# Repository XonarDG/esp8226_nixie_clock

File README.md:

# esp8266_nixie_clock

Simple Nixie Clock with an ESP8266 development board

## Info

This is a small project for a simple nixie clock using a ESP8266 development board. **WIP! USE AS REFERENCE ONLY!**

## Why?
Like many others, I've fallen for the look of nixies way before this project began. At the time I thought I wasn't capable of a project like this, but in late 2021 I made my first prototype using MH74141 and Tesla ZM1020 nixies. It was rough, didn't work properly and was on a protoboard, but it motivated me into doing more.

In 2024 I made the decision to make this my high school graduation project and this is what came out of it. It still has rough edges here and there, but it works, and it has a somewhat complete enclosure.

At this point I thought it would be a nice touch making the project publicly available. That said its far from done, and I would not recommend making this project on your own.

## Parts
Name | Designation | #
--- | --- | ---
MCU | Wemos D1 Mini | 1
RTC module | generic DS3231 | 1
Shift Register | 74HC595 | 3
Cathode transistors | MPSA42 | 10
Anode optoucouplers | TLP627 | 6
Voltage Regulator | AMS1117 3.3 | 1
Resistor | various values | 26
Pin header (male) | generic 2.54mm | 21
Pin header (famale) | generic 2.54mm | 46

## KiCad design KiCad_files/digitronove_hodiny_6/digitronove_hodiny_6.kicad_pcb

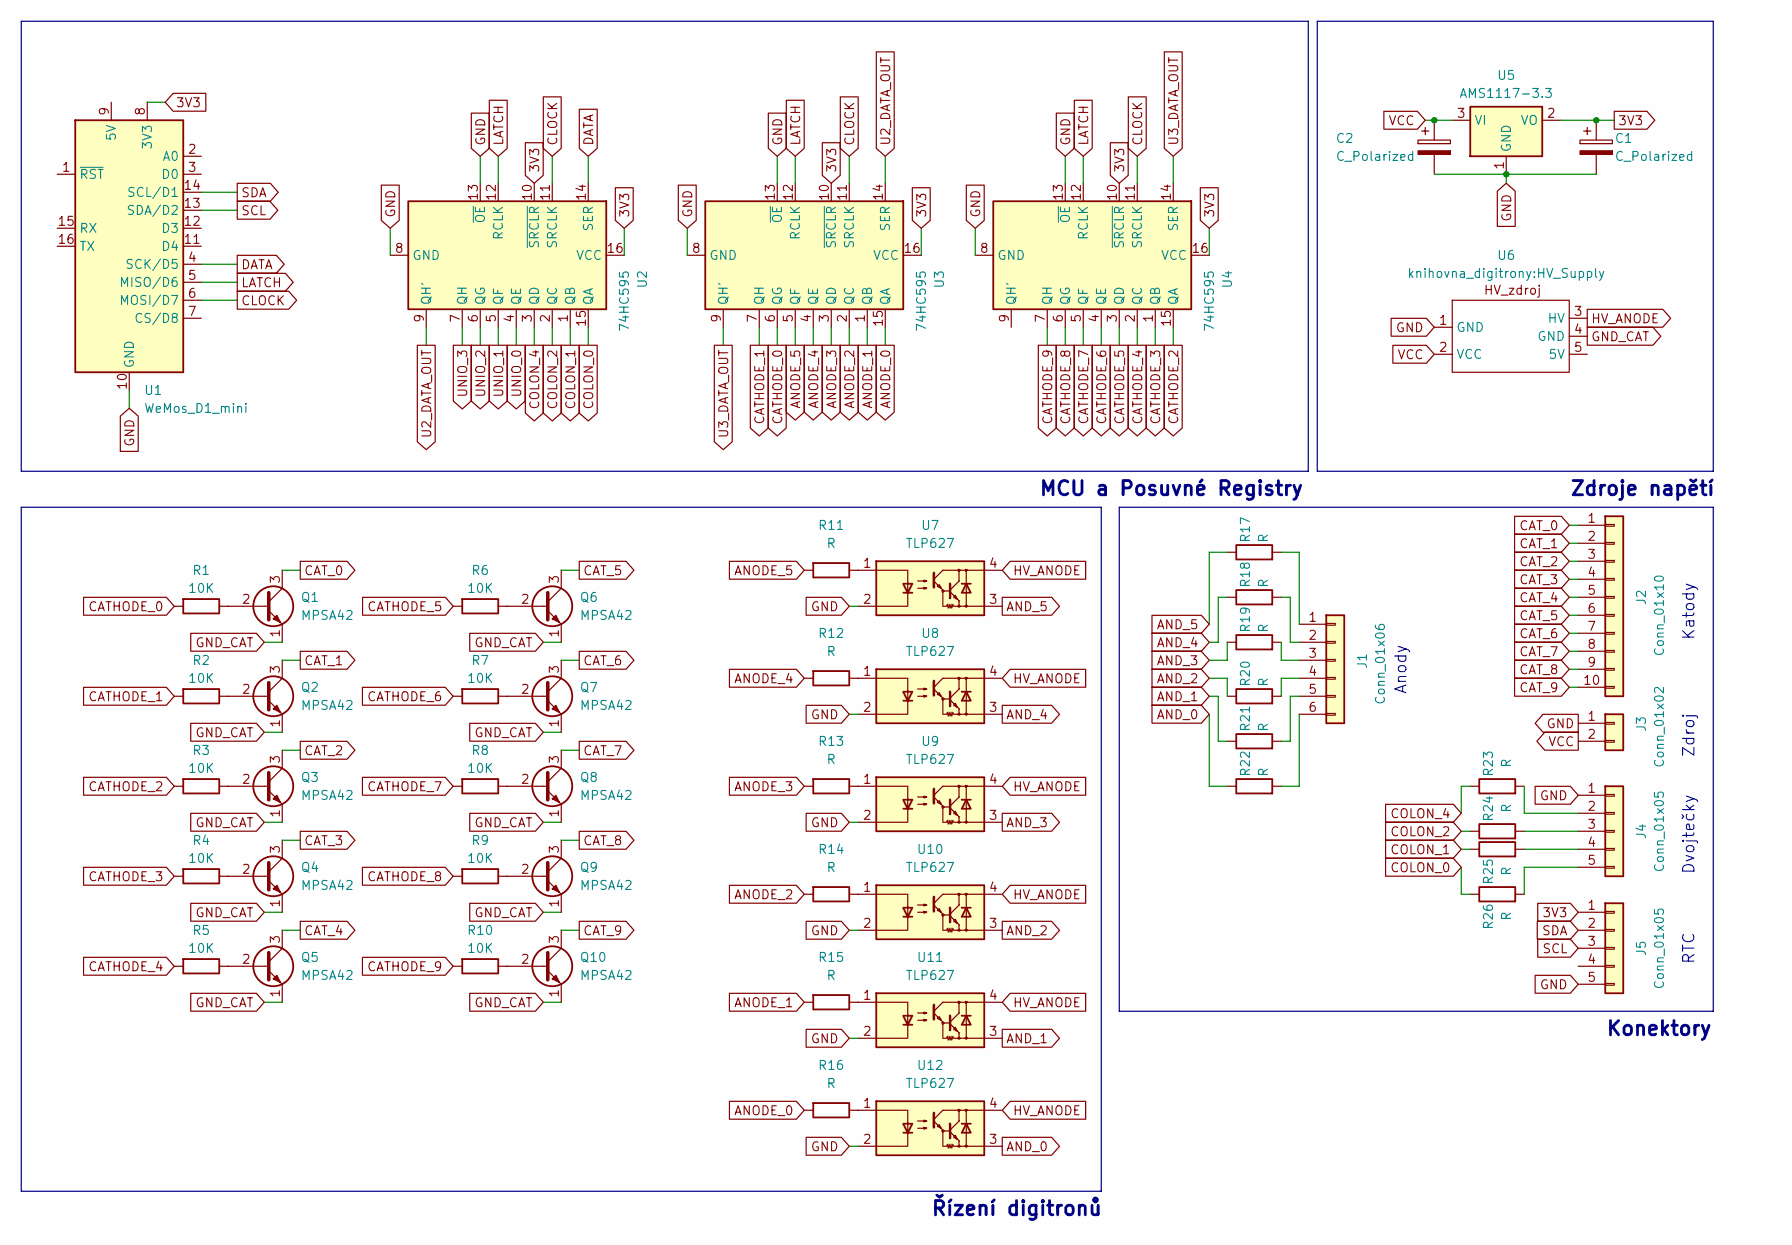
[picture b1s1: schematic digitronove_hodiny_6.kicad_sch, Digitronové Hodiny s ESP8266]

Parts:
C1, C2: C_Polarized; CP_Radial_Tantal_D5.5mm_P2.50mm
J1: Conn_01x06; PinHeader_1x06_P2.54mm_Vertical
J2: Conn_01x10; PinHeader_1x10_P2.54mm_Vertical
J3: Conn_01x02; PinHeader_1x02_P2.54mm_Vertical
J4, J5: Conn_01x05; PinHeader_1x05_P2.54mm_Vertical
Q1, Q2, Q3, Q4, Q5, Q6, Q7, Q8, Q9, Q10: MPSA42; TO-92_Inline_Wide
R1, R2, R3, R4, R5, R6, R7, R8, R9, R10: 10K; R_Axial_DIN0204_L3.6mm_D1.6mm_P7.62mm_Horizontal
R11, R12, R13, R14, R15, R16, R17, R18, R19, R20, R21, R22, R23, R24, R25, R26: R; R_Axial_DIN0204_L3.6mm_D1.6mm_P7.62mm_Horizontal
U1: WeMos_D1_mini; WEMOS_D1_mini_light
U2, U3, U4: 74HC595; DIP-16_W7.62mm
U5: AMS1117-3.3; SOT-223-3_TabPin2
U6: HV_Supply
U7, U8, U9, U10, U11, U12: TLP627; DIP-4_W7.62mm

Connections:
3V3: C1.1, J5.1, U1.8 (3V3), U2.10 (~SRCLR), U2.16 (VCC), U3.10 (~SRCLR), U3.16 (VCC), U4.10 (~SRCLR), U4.16 (VCC), U5.2 (VO)
AND_0: R22.1, U12.3
AND_1: R21.1, U11.3
AND_2: R20.1, U10.3
AND_3: R19.1, U9.3
AND_4: R18.1, U8.3
AND_5: R17.1, U7.3
ANODE_0: R16.2, U3.15 (QA)
ANODE_1: R15.2, U3.1 (QB)
ANODE_2: R14.2, U3.2 (QC)
ANODE_3: R13.2, U3.3 (QD)
ANODE_4: R12.2, U3.4 (QE)
ANODE_5: R11.2, U3.5 (QF)
CATHODE_0: R1.2, U3.6 (QG)
CATHODE_1: R2.2, U3.7 (QH)
CATHODE_2: R3.2, U4.15 (QA)
CATHODE_3: R4.2, U4.1 (QB)
CATHODE_4: R5.2, U4.2 (QC)
CATHODE_5: R6.2, U4.3 (QD)
CATHODE_6: R7.2, U4.4 (QE)
CATHODE_7: R8.2, U4.5 (QF)
CATHODE_8: R9.2, U4.6 (QG)
CATHODE_9: R10.2, U4.7 (QH)
CAT_0: J2.1, Q1.3 (C)
CAT_1: J2.2, Q2.3 (C)
CAT_2: J2.3, Q3.3 (C)
CAT_3: J2.4, Q4.3 (C)
CAT_4: J2.5, Q5.3 (C)
CAT_5: J2.6, Q6.3 (C)
CAT_6: J2.7, Q7.3 (C)
CAT_7: J2.8, Q8.3 (C)
CAT_8: J2.9, Q9.3 (C)
CAT_9: J2.10, Q10.3 (C)
CLOCK: U1.6 (MOSI/D7), U2.11 (SRCLK), U3.11 (SRCLK), U4.11 (SRCLK)
COLON_0: R26.1, U2.15 (QA)
COLON_1: R25.1, U2.1 (QB)
COLON_2: R24.1, U2.2 (QC)
COLON_4: R23.1, U2.3 (QD)
DATA: U1.4 (SCK/D5), U2.14 (SER)
GND: C1.2, C2.2, J3.1, J4.1, J5.5, U1.10 (GND), U2.8 (GND), U2.13 (~OE), U3.8 (GND), U3.13 (~OE), U4.8 (GND), U4.13 (~OE), U5.1 (GND), U6.1 (GND), U7.2, U8.2, U9.2, U10.2, U11.2, U12.2
GND_CAT: Q1.1 (E), Q2.1 (E), Q3.1 (E), Q4.1 (E), Q5.1 (E), Q6.1 (E), Q7.1 (E), Q8.1 (E), Q9.1 (E), Q10.1 (E), U6.4 (GND)
HV_ANODE: U6.3 (HV), U7.4, U8.4, U9.4, U10.4, U11.4, U12.4
LATCH: U1.5 (MISO/D6), U2.12 (RCLK), U3.12 (RCLK), U4.12 (RCLK)
unnamed: J1.1, R17.2
unnamed: J1.2, R18.2
unnamed: J1.3, R19.2
unnamed: J1.4, R20.2
unnamed: J1.5, R21.2
unnamed: J1.6, R22.2
unnamed: J4.2, R23.2
unnamed: J4.3, R24.2
unnamed: J4.4, R25.2
unnamed: J4.5, R26.2
unnamed: Q1.2 (B), R1.1
unnamed: Q2.2 (B), R2.1
unnamed: Q3.2 (B), R3.1
unnamed: Q4.2 (B), R4.1
unnamed: Q5.2 (B), R5.1
unnamed: Q6.2 (B), R6.1
unnamed: Q7.2 (B), R7.1
unnamed: Q8.2 (B), R8.1
unnamed: Q9.2 (B), R9.1
unnamed: Q10.2 (B), R10.1
unnamed: R11.1, U7.1
unnamed: R12.1, U8.1
unnamed: R13.1, U9.1
unnamed: R14.1, U10.1
unnamed: R15.1, U11.1
unnamed: R16.1, U12.1
SCL: J5.3, U1.13 (SDA/D2)
SDA: J5.2, U1.14 (SCL/D1)
U2_DATA_OUT: U2.9 (QH'), U3.14 (SER)
U3_DATA_OUT: U3.9 (QH'), U4.14 (SER)
UNIO_0: U2.4 (QE)
UNIO_1: U2.5 (QF)
UNIO_2: U2.6 (QG)
UNIO_3: U2.7 (QH)
VCC: C2.1, J3.2, U5.3 (VI), U6.2 (VCC)

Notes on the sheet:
Zdroje napětí
RTC
Anody
Řízení digitronů
Zdroj
Konektory
Katody
Dvojtečky
MCU a Posuvné Registry

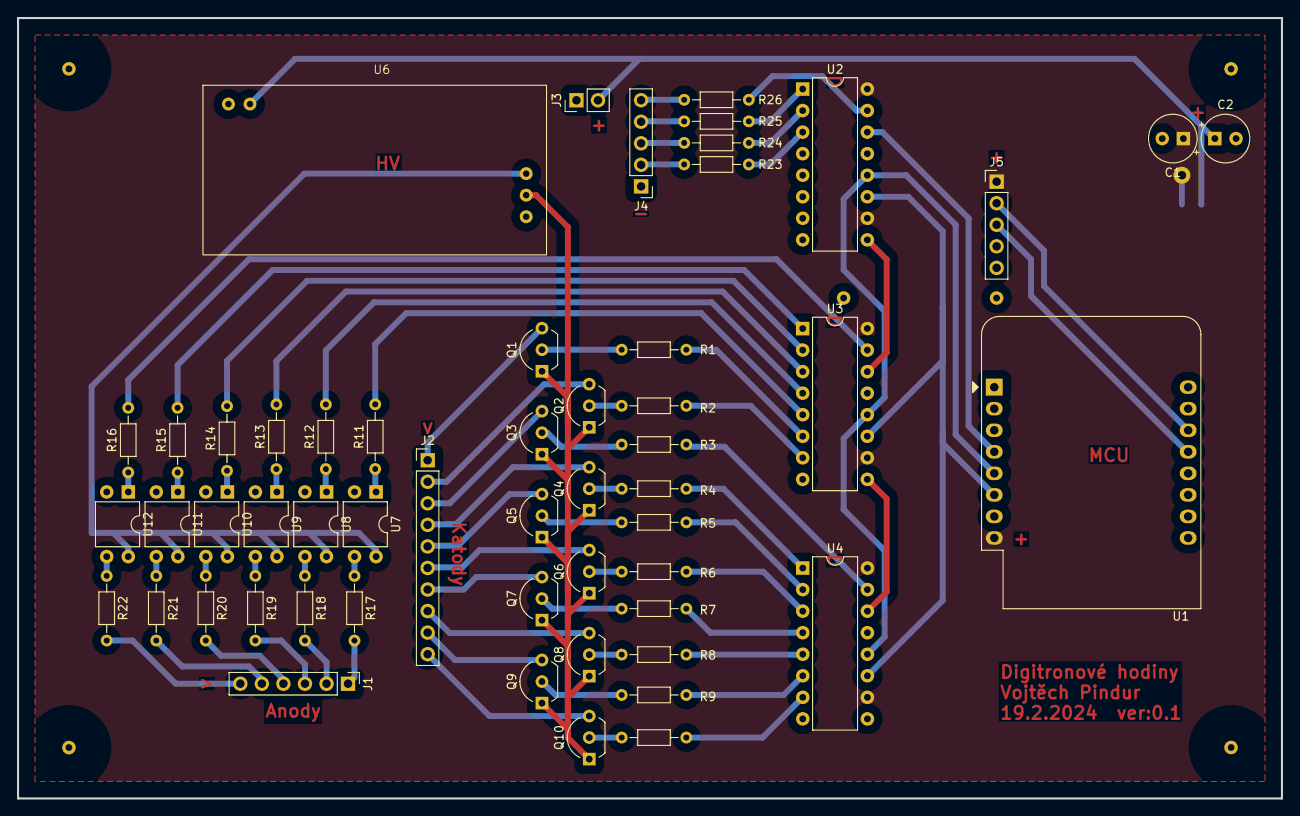
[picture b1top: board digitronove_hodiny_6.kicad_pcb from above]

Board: 2 copper layers, 149.0 x 92.0 mm, 55 parts (1 on the bottom side), 74 nets.

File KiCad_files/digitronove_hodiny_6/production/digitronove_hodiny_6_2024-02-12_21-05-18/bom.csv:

Designator,Footprint,Quantity,Value,LCSC Part #
,,1,,
C2,CP_Radial_Tantal_D5.5mm_P2.50mm,1,C_Polarized,
J1,PinHeader_1x10_P2.54mm_Vertical,1,Nixie_CATHODES,
J2,PinHeader_1x06_P2.54mm_Vertical,1,Nixie_ANODES,
"J3, J4",PinHeader_1x05_P2.54mm_Vertical,2,Conn_01x05,
J5,PinHeader_1x02_P2.54mm_Vertical,1,Conn_01x02,
"Q1, Q10, Q2, Q3, Q4, Q5, Q6, Q7, Q8, Q9",TO-92_Inline,10,MPSA42,
"R1, R10, R2, R3, R4, R5, R6, R7, R8, R9",R_Axial_DIN0204_L3.6mm_D1.6mm_P7.62mm_Horizontal,10,10K,
"R11, R12, R13, R14, R15, R16, R17, R18, R19, R20, R21, R22, R23, R24, R25, R26",R_Axial_DIN0204_L3.6mm_D1.6mm_P7.62mm_Horizontal,16,R,
U1,WEMOS_D1_mini_light,1,WeMos_D1_mini,
"U10, U2, U3",DIP-16_W7.62mm,3,74HC595,
U11,HV_Supply,1,~,
U12,SOT-223-3_TabPin2,1,AMS1117-3.3,
"U4, U5, U6, U7, U8, U9",DIP-4_W7.62mm,6,TLP627,

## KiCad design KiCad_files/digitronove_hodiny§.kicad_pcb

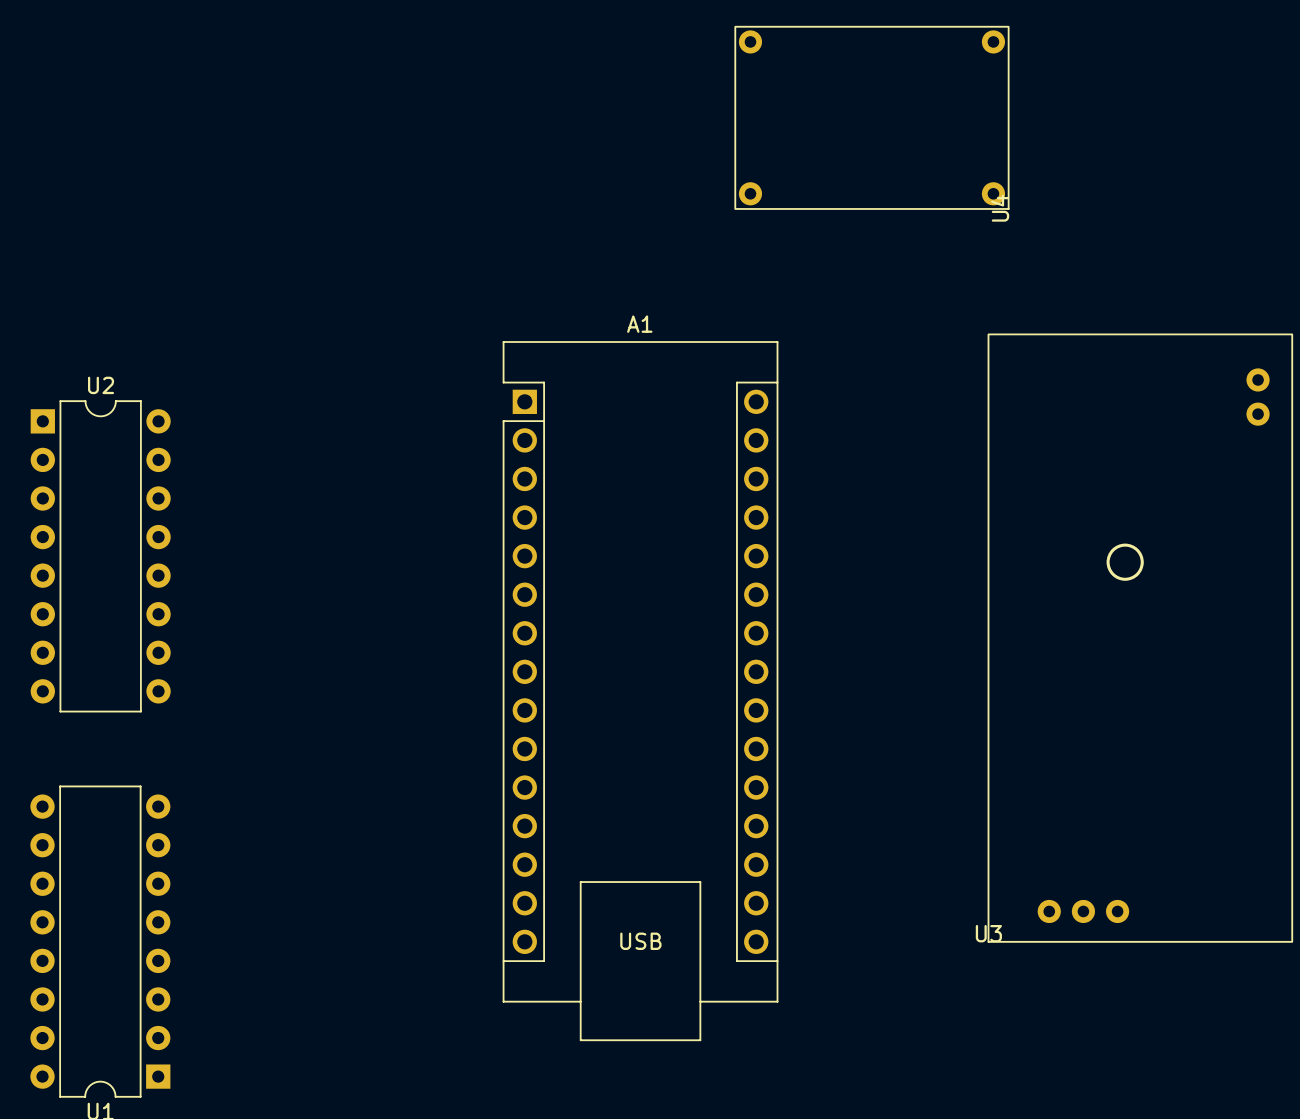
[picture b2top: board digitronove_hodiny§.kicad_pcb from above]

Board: 2 copper layers, 5 parts (0 on the bottom side), 12 nets, no tracks yet.

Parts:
A1: Arduino_Nano_Every; Arduino_Nano
U1: 74141; DIP-16_W7.62mm
U2: TLP627-4; DIP-16_W7.62mm
U3: HV_supply_module
U4: Mini360; DC-DC_MINI_360_Step_down

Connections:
GND: A1.4 (GND), A1.29 (GND), U1.12 (GND), U2.2, U2.4, U2.6, U2.8, U4.1 (GND)
unnamed: A1.7 (D4), U2.3
unnamed: A1.8 (D5), U2.5
unnamed: A1.9 (D6), U2.7
unnamed: A1.10 (D7), U1.3 (A)
unnamed: A1.11 (D8), U1.6 (B)
unnamed: A1.12 (D9), U1.7 (C)
unnamed: A1.13 (D10), U1.4 (D)
unnamed: A1.30 (VIN), U4.3 (VOUT)
unnamed: A1.6 (D3), U2.1
unnamed: U2.10, U2.12, U2.14, U2.16, U3.3 (HV)
VCC: A1.27 (+5V), U1.5 (VCC), U3.5 (VCC), U4.2 (VCC)

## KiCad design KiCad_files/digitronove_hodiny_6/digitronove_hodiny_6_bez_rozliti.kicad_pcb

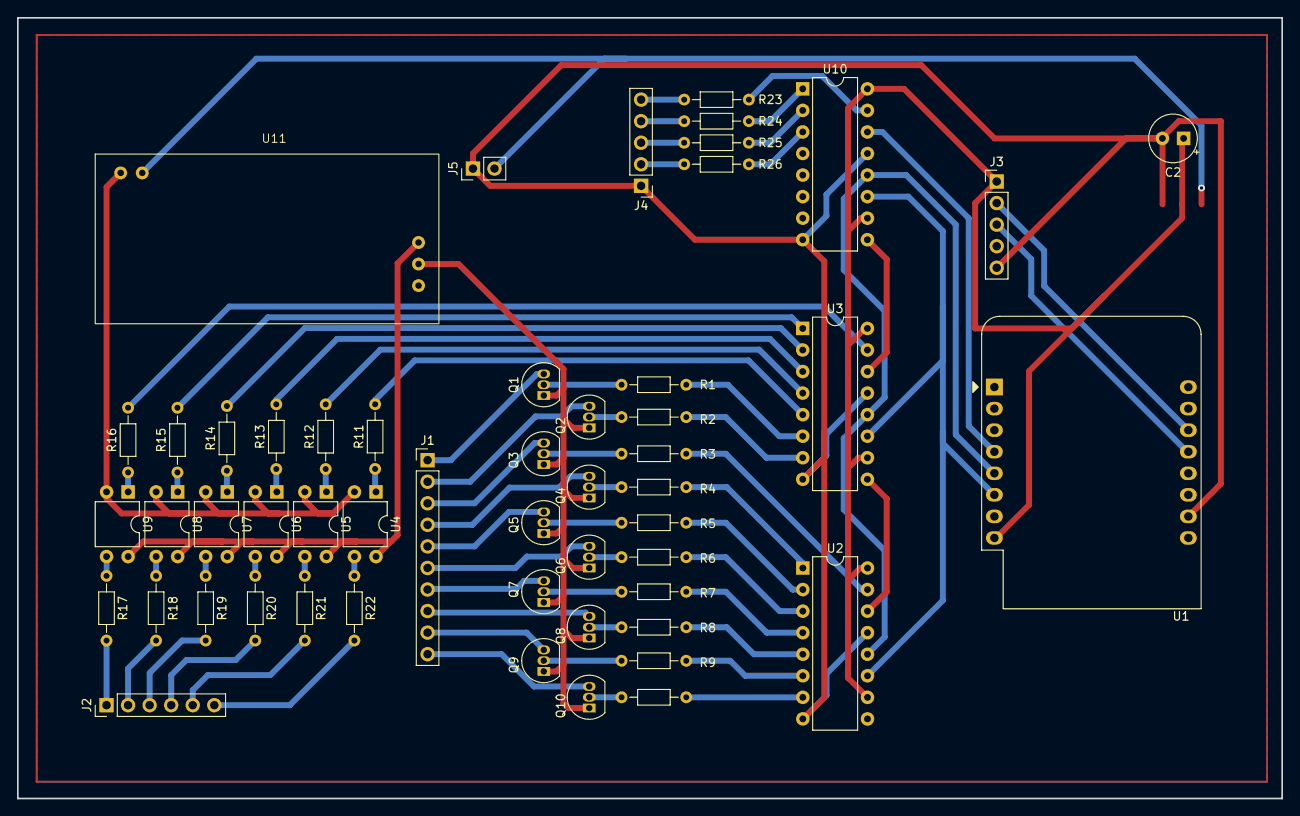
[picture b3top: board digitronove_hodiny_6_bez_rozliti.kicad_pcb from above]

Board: 2 copper layers, 149.0 x 92.0 mm, 54 parts (1 on the bottom side), 74 nets.

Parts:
C2: C_Polarized; CP_Radial_Tantal_D5.5mm_P2.50mm
J1: Nixie_CATHODES; PinHeader_1x10_P2.54mm_Vertical
J2: Nixie_ANODES; PinHeader_1x06_P2.54mm_Vertical
J3, J4: Conn_01x05; PinHeader_1x05_P2.54mm_Vertical
J5: Conn_01x02; PinHeader_1x02_P2.54mm_Vertical
Q1, Q2, Q3, Q4, Q5, Q6, Q7, Q8, Q9, Q10: MPSA42; TO-92_Inline
R1, R2, R3, R4, R5, R6, R7, R8, R9, R10: 10K; R_Axial_DIN0204_L3.6mm_D1.6mm_P7.62mm_Horizontal
R11, R12, R13, R14, R15, R16, R17, R18, R19, R20, R21, R22, R23, R24, R25, R26: R; R_Axial_DIN0204_L3.6mm_D1.6mm_P7.62mm_Horizontal
U1: WeMos_D1_mini; WEMOS_D1_mini_light
U2, U3, U10: 74HC595; DIP-16_W7.62mm
U4, U5, U6, U7, U8, U9: TLP627; DIP-4_W7.62mm
U11: HV_Supply
U12: AMS1117-3.3; SOT-223-3_TabPin2

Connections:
3V3: C2.1, J3.1, U1.8 (3V3), U2.10 (~SRCLR), U2.16 (VCC), U3.10 (~SRCLR), U3.16 (VCC), U10.10 (~SRCLR), U10.16 (VCC), U12.2 (VO)
AND_0: R17.1, U9.3
AND_1: R18.1, U8.3
AND_2: R19.1, U7.3
AND_3: R20.1, U6.3
AND_4: R21.1, U5.3
AND_5: R22.1, U4.3
ANODE_0: R16.2, U3.15 (QA)
ANODE_1: R15.2, U3.1 (QB)
ANODE_2: R14.2, U3.2 (QC)
ANODE_3: R13.2, U3.3 (QD)
ANODE_4: R12.2, U3.4 (QE)
ANODE_5: R11.2, U3.5 (QF)
CATHODE_0: R1.2, U3.6 (QG)
CATHODE_1: R2.2, U3.7 (QH)
CATHODE_2: R3.2, U2.15 (QA)
CATHODE_3: R4.2, U2.1 (QB)
CATHODE_4: R5.2, U2.2 (QC)
CATHODE_5: R6.2, U2.3 (QD)
CATHODE_6: R7.2, U2.4 (QE)
CATHODE_7: R8.2, U2.5 (QF)
CATHODE_8: R9.2, U2.6 (QG)
CATHODE_9: R10.2, U2.7 (QH)
CAT_0: J1.1, Q1.3 (C)
CAT_1: J1.2, Q2.3 (C)
CAT_2: J1.3, Q3.3 (C)
CAT_3: J1.4, Q4.3 (C)
CAT_4: J1.5, Q5.3 (C)
CAT_5: J1.6, Q6.3 (C)
CAT_6: J1.7, Q7.3 (C)
CAT_7: J1.8, Q8.3 (C)
CAT_8: J1.9, Q9.3 (C)
CAT_9: J1.10, Q10.3 (C)
CLOCK: U1.6 (MOSI/D7), U2.11 (SRCLK), U3.11 (SRCLK), U10.11 (SRCLK)
COLON_0: R23.1, U10.15 (QA)
COLON_1: R24.1, U10.1 (QB)
COLON_2: R25.1, U10.2 (QC)
COLON_4: R26.1, U10.3 (QD)
DATA: U1.4 (SCK/D5), U10.14 (SER)
GND: C2.2, J3.5, J4.1, J5.1, U1.10 (GND), U2.8 (GND), U2.13 (~OE), U3.8 (GND), U3.13 (~OE), U4.2, U5.2, U6.2, U7.2, U8.2, U9.2, U10.8 (GND), U10.13 (~OE), U11.1 (GND), U12.1 (GND)
GND_CAT: Q1.1 (E), Q2.1 (E), Q3.1 (E), Q4.1 (E), Q5.1 (E), Q6.1 (E), Q7.1 (E), Q8.1 (E), Q9.1 (E), Q10.1 (E), U11.4 (GND)
HV_ANODE: U4.4, U5.4, U6.4, U7.4, U8.4, U9.4, U11.3 (HV)
LATCH: U1.5 (MISO/D6), U2.12 (RCLK), U3.12 (RCLK), U10.12 (RCLK)
unnamed: J2.1, R17.2
unnamed: J2.2, R18.2
unnamed: J2.3, R19.2
unnamed: J2.4, R20.2
unnamed: J2.5, R21.2
unnamed: J2.6, R22.2
unnamed: J4.2, R26.2
unnamed: J4.3, R25.2
unnamed: J4.4, R24.2
unnamed: J4.5, R23.2
unnamed: Q1.2 (B), R1.1
unnamed: Q2.2 (B), R2.1
unnamed: Q3.2 (B), R3.1
unnamed: Q4.2 (B), R4.1
unnamed: Q5.2 (B), R5.1
unnamed: Q6.2 (B), R6.1
unnamed: Q7.2 (B), R7.1
unnamed: Q8.2 (B), R8.1
unnamed: Q9.2 (B), R9.1
unnamed: Q10.2 (B), R10.1
unnamed: R11.1, U4.1
unnamed: R12.1, U5.1
unnamed: R13.1, U6.1
unnamed: R14.1, U7.1
unnamed: R15.1, U8.1
unnamed: R16.1, U9.1
SCL: J3.3, U1.13 (SDA/D2)
SDA: J3.2, U1.14 (SCL/D1)
U2_DATA_OUT: U3.14 (SER), U10.9 (QH')
U3_DATA_OUT: U2.14 (SER), U3.9 (QH')
VCC: J5.2, U11.2 (VCC), U12.3 (VI)

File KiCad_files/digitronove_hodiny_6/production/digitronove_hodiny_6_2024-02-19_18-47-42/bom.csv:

Designator,Footprint,Quantity,Value,LCSC Part #
"_7, _6, _5, _4, _3, _2, ",,7,,
"C1, C2",CP_Radial_Tantal_D5.5mm_P2.50mm,2,C_Polarized,
J1,PinHeader_1x06_P2.54mm_Vertical,1,Conn_01x06,
J2,PinHeader_1x10_P2.54mm_Vertical,1,Conn_01x10,
J3,PinHeader_1x02_P2.54mm_Vertical,1,Conn_01x02,
"J4, J5",PinHeader_1x05_P2.54mm_Vertical,2,Conn_01x05,
"Q1, Q10, Q2, Q3, Q4, Q5, Q6, Q7, Q8, Q9",TO-92_Inline_Wide,10,MPSA42,
"R1, R10, R2, R3, R4, R5, R6, R7, R8, R9",R_Axial_DIN0204_L3.6mm_D1.6mm_P7.62mm_Horizontal,10,10K,
"R11, R12, R13, R14, R15, R16, R17, R18, R19, R20, R21, R22, R23, R24, R25, R26",R_Axial_DIN0204_L3.6mm_D1.6mm_P7.62mm_Horizontal,16,R,
U1,WEMOS_D1_mini_light,1,WeMos_D1_mini,
"U10, U11, U12, U7, U8, U9",DIP-4_W7.62mm,6,TLP627,
"U2, U3, U4",DIP-16_W7.62mm,3,74HC595,
U5,SOT-223-3_TabPin2,1,AMS1117-3.3,
U6,HV_Supply,1,~,

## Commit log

2022-12-16 Initial changes to README.md
    Basic Plan and decision making.
2022-12-16 README.md update.
2022-12-18 README.md changes.
2022-12-18 Created 'KiCad_files' directory and added initital files.
2022-12-18 Added proprietary symbols and footprints.
2022-12-18 Added KiCad project as a .zip
2022-12-19 Updated .zip file.
2022-12-22 README.md update
2022-12-22 Updated .zip containing KiCad project
2022-12-22 Added WIP PlatformIO project
2022-12-25 Updated the code
2022-12-25 Added cathode protection feature
2022-12-26 Improved AllNumbers method, added ShowDate method.
2022-12-28 Updated code, added and improved methods.
    Adapted the code to use methods only, makes it a bit more clean.
2022-12-28 Fixed wrong input for AllNumbers method.
2022-12-28 Fixed 'AllNumbers not launching' bug.
2023-01-02 Troubleshooting WIP code, added .stl file.
    Trying to trouble shoot nixie ghosting, added a protoype front panel model to print. More info about in DOCS.md
2023-01-03 Colon method now using unix_time,
2023-01-10 Added test code.
2023-01-10 Moved Colon().
2023-02-02 general bug fixing
2023-02-02 Changed RTC
2023-02-02 Sync commit.
2023-04-19 BIG update!
    Added an entire ESP-32 version of the code that has been rewritten a couple of times. The core is the same but I added a NTP to update the RTC every 6 hours.
2023-04-19 Small change.
2023-04-24 Started writing code.md
2023-10-17 Bug fixes.
2024-01-19 Big update.
    Some development has been done on the project. I'll be abandoning the ESP32 version of the project now, since I've moved to an entire different way of doing things. Read more in README.
2024-01-22 Dev_commit
2024-01-29 Code update.
2024-01-31 Added new KiCad files.
2024-02-05 KiCad PCB and Schema desing update
    Nearly finished PCB desing. Changed the schema according to my breadboard prototype.
2024-02-06 PCB Update
2024-02-12 General changes.
    Removed some unnecesary files, minor changes to PCB design, added a 3D Model directory for future files.
2024-02-18 Created resources directory, EDA files update.
2024-02-20 PCB Design update
2024-03-28 Code and PCB update
2024-04-01 Small updates to code
2024-04-23 Added repo_sources directory
    for images or other needed files not directly needed for the project
2024-05-21 Code and README updates
2024-05-22 file changes in the kicad section
2024-05-22 Removed unnecessary files from EDA files.
